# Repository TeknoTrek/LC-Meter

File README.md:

# DIY LC Meter Project

This project demonstrates how to build a DIY LC Meter capable of measuring inductance (L) and capacitance (C) values using an Arduino Nano, an LM311 comparator, and a 16x2 LCD display. The LC Meter is designed to be simple, affordable, and effective for electronics enthusiasts and DIY hobbyists. It is suitable for learning about measurement principles while also being a practical tool.

## Project Highlights:

### 1 - Circuit Schematic
A detailed circuit diagram explains the working principle and interconnection of components such as the LM311 comparator, relay, calibration buttons, and measurement probes. The schematic provides a foundation for assembling the hardware.

### 2 - PCB Design
A professionally designed single-layer PCB created with KiCad ensures clean routing and minimizes interference. It includes detailed silkscreen labels for easy assembly and debugging.

### 3 - 3D Model
A realistic 3D representation of the completed PCB with components mounted, offering a clear view of the final product and component placement.

### 4 - Firmware
The Arduino Nano is programmed with custom firmware to calculate inductance and capacitance values. Measurements are displayed on a 16x2 LCD in real time.

### 5 - Calibration and Functionality
The project includes functionality for calibration, zeroing, and easy measurement. Buttons on the PCB allow users to fine-tune settings for accurate results.

---

### Features:
- Precise Measurements: Measure a wide range of inductance and capacitance values.
- User-Friendly Interface: Includes a 16x2 LCD display for real-time measurement results and intuitive feedback.
- Adjustable Calibration: Easily calibrate the device for accurate readings using the on-board calibration buttons.
- Compact and Portable: The design is compact, making it easy to use in different workspaces or carry for fieldwork.

### Instructions:
### Prepare the PCB:
Download the provided Gerber files and manufacture the PCB, or use the KiCad design to etch your own board.

### Assemble Components:
Place and solder all components as per the silkscreen labels on the PCB.

### Upload Firmware:
Use the Arduino IDE to upload the provided sketch to your Arduino Nano. Ensure all libraries are correctly installed.

### Power and Calibration:
Connect the LC Meter to a 5V power source via USB or the provided input terminals. Calibrate the device using the calibration and zero buttons for precise results.

### Start Measuring:
Connect your inductors or capacitors to the respective terminals (Lx or Cx) and observe the measurement results on the LCD.

## Watch the Build Process

You can watch the full build process of this DIY LC Meter on my YouTube channel [**Teknotrek**](https://www.youtube.com/@TeknoTrek). Click the link below to see how the circuit is assembled, soldered, and tested:

[Watch on YouTube](https://youtu.be/YbbpxDlLRkQ)

## Files Included:
- Circuit schematic
- PCB design files (KiCad)
- 3D PCB model
- Arduino firmware
- Documentation with detailed assembly and usage instructions

## Circuit Schematic

## PCB Layout

## 3D Model

## GitHub Repository:
All project files, including schematics, PCB designs, 3D models, and source code, are available on GitHub.

Check out the project here: [**Teknotrek**](https://www.youtube.com/@TeknoTrek)

This project is perfect for anyone interested in electronics, DIY tools, or Arduino projects. Whether you are a beginner or an experienced maker,this LC Meter provides a hands-on learning experience and a functional tool for your electronics toolkit!

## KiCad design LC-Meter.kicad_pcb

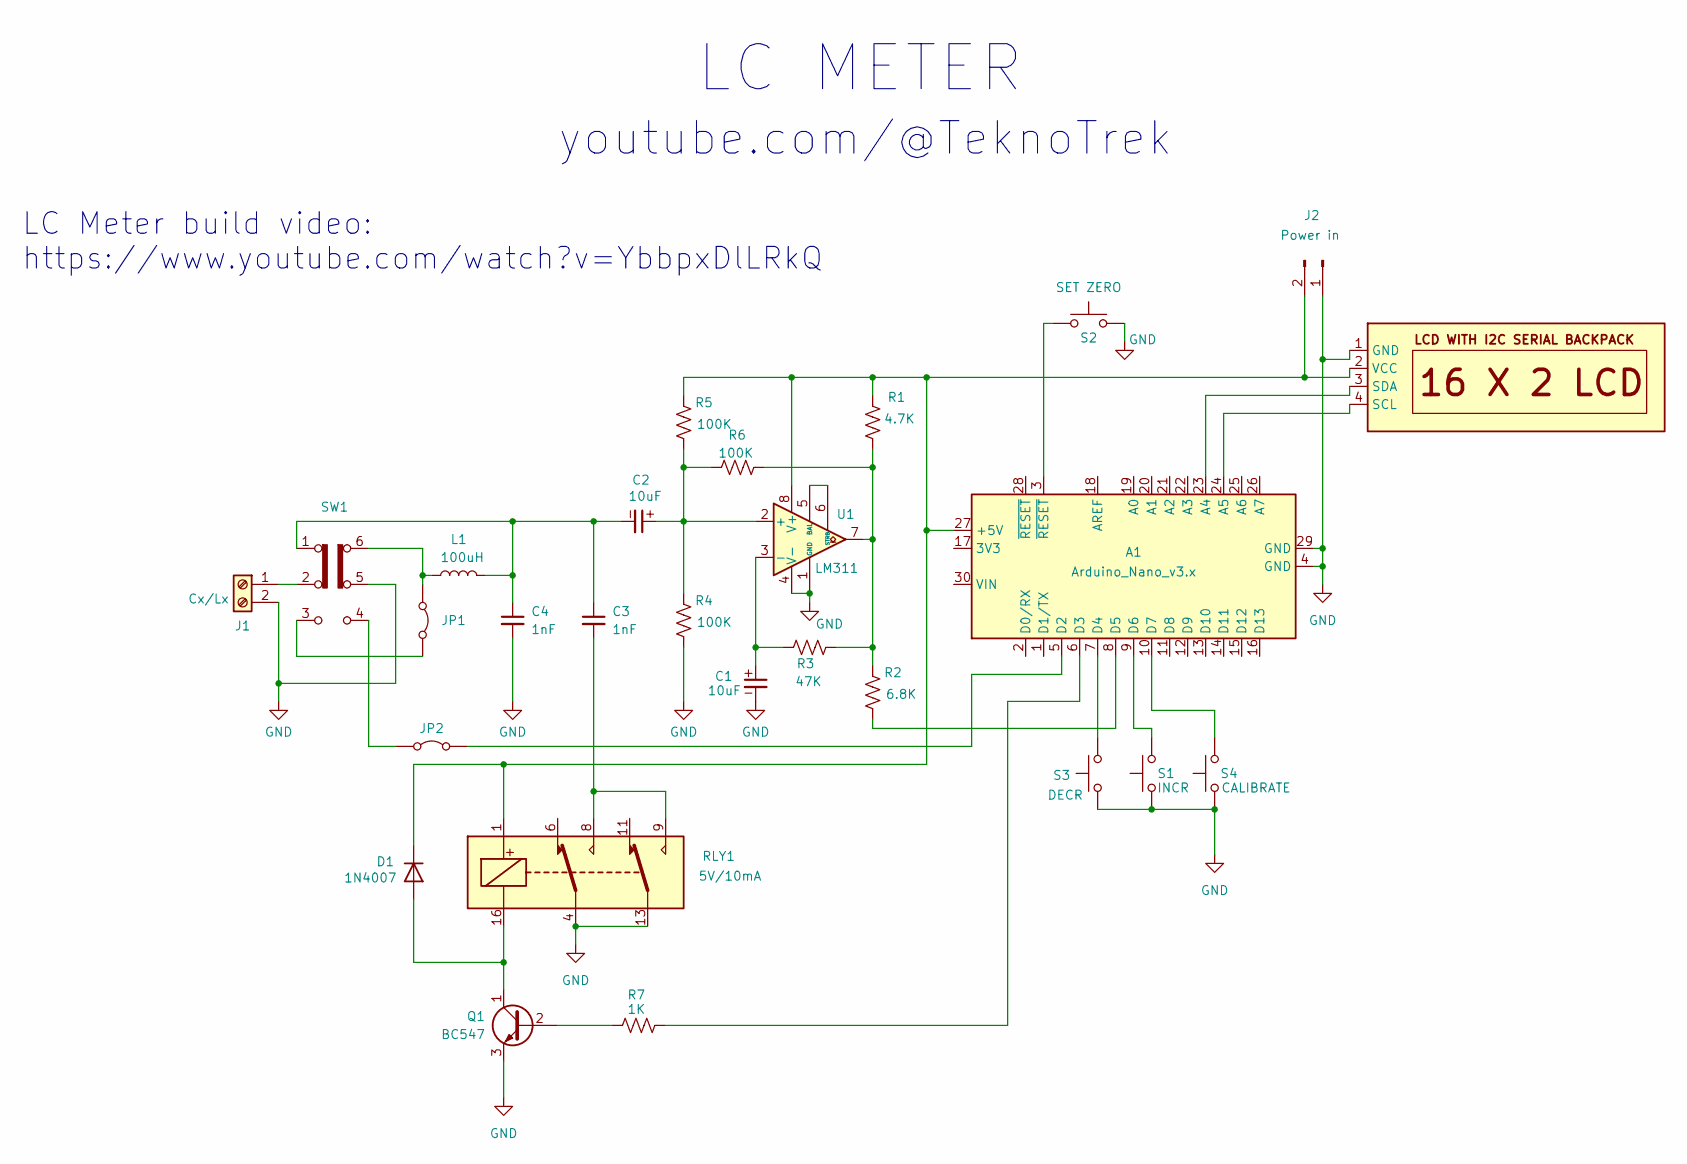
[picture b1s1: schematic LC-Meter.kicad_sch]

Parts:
A1: Arduino_Nano_v3.x; Arduino_Nano
C1, C2: 10uF; CP_Radial_Tantal_D4.5mm_P2.50mm
C3, C4: 1nF; CP_Radial_Tantal_D5.0mm_P5.00mm
D1: 1N4007; D_DO-41_SOD81_P10.16mm_Horizontal
DS1: WC1602A-I2C
J1: Cx/Lx; TerminalBlock_bornier-2_P5.08mm
J2: Power in; PinSocket_1x02_P2.54mm_Vertical
JP1, JP2: Jumper_2; R_Axial_DIN0207_L6.3mm_D2.5mm_P10.16mm_Horizontal
L1: 100uH; L_Axial_L5.3mm_D2.2mm_P10.16mm_Horizontal_Vishay_IM-1
Q1: BC547; TO-92_Wide
R1: 4.7K; R_Axial_DIN0207_L6.3mm_D2.5mm_P10.16mm_Horizontal
R2: 6.8K; R_Axial_DIN0207_L6.3mm_D2.5mm_P10.16mm_Horizontal
R3: 47K; R_Axial_DIN0207_L6.3mm_D2.5mm_P10.16mm_Horizontal
R4, R5, R6: 100K; R_Axial_DIN0207_L6.3mm_D2.5mm_P10.16mm_Horizontal
R7: 1K; R_Axial_DIN0207_L6.3mm_D2.5mm_P10.16mm_Horizontal
RLY1: 5V/10mA; TIANBO-HJR1-2CL-05V-footer
S1: INCR; SW_PUSH-12mm
S2: SET ZERO; SW_PUSH-12mm
S3: DECR; SW_PUSH-12mm
S4: CALIBRATE; SW_PUSH-12mm
SW1: SW_Slide_DPDT; SW_CK_
U1: LM311; DIP-8_W7.62mm

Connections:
GND: A1.4 (GND), A1.29 (GND), C1.2, C4.2, DS1.1 (GND), J1.2, J2.1, Q1.3 (E), R4.2, RLY1.4, RLY1.13, S1.1, S2.2, S3.1, S4.1, SW1.5 (B), U1.1 (GND), U1.4 (V-)
unnamed: A1.27 (+5V), D1.1 (K), DS1.2 (VCC), J2.2, R1.1, R5.1, RLY1.1, U1.8 (V+)
unnamed: A1.23 (A4), DS1.3 (SDA)
unnamed: A1.24 (A5), DS1.4 (SCL)
unnamed: A1.5 (D2), JP2.2 (B)
unnamed: A1.6 (D3), R7.2
unnamed: A1.7 (D4), S3.2
unnamed: A1.8 (D5), R2.2
unnamed: A1.9 (D6), S1.2
unnamed: A1.10 (D7), S4.2
unnamed: A1.3 (~RESET), S2.1
unnamed: C2.2, C3.1, C4.1, L1.2, SW1.1 (A)
unnamed: C3.2, RLY1.8, RLY1.9
unnamed: D1.2 (A), Q1.1 (C), RLY1.16
unnamed: J1.1, SW1.2 (B)
unnamed: JP1.1 (A), L1.1, SW1.6 (C)
unnamed: JP1.2 (B), SW1.3 (C)
unnamed: JP2.1 (A), SW1.4 (A)
unnamed: Q1.2 (B), R7.1
unnamed: R1.2, R2.1, R3.2, R6.2, U1.7
unnamed: C2.1, R4.1, R5.2, R6.1, U1.2 (+)
unnamed: C1.1, R3.1, U1.3 (-)
unnamed: U1.5 (BAL), U1.6 (STRB)

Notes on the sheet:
LC Meter build video: https://www.youtube.com/watch?v=YbbpxDlLRkQ
youtube.com/@TeknoTrek
LC METER

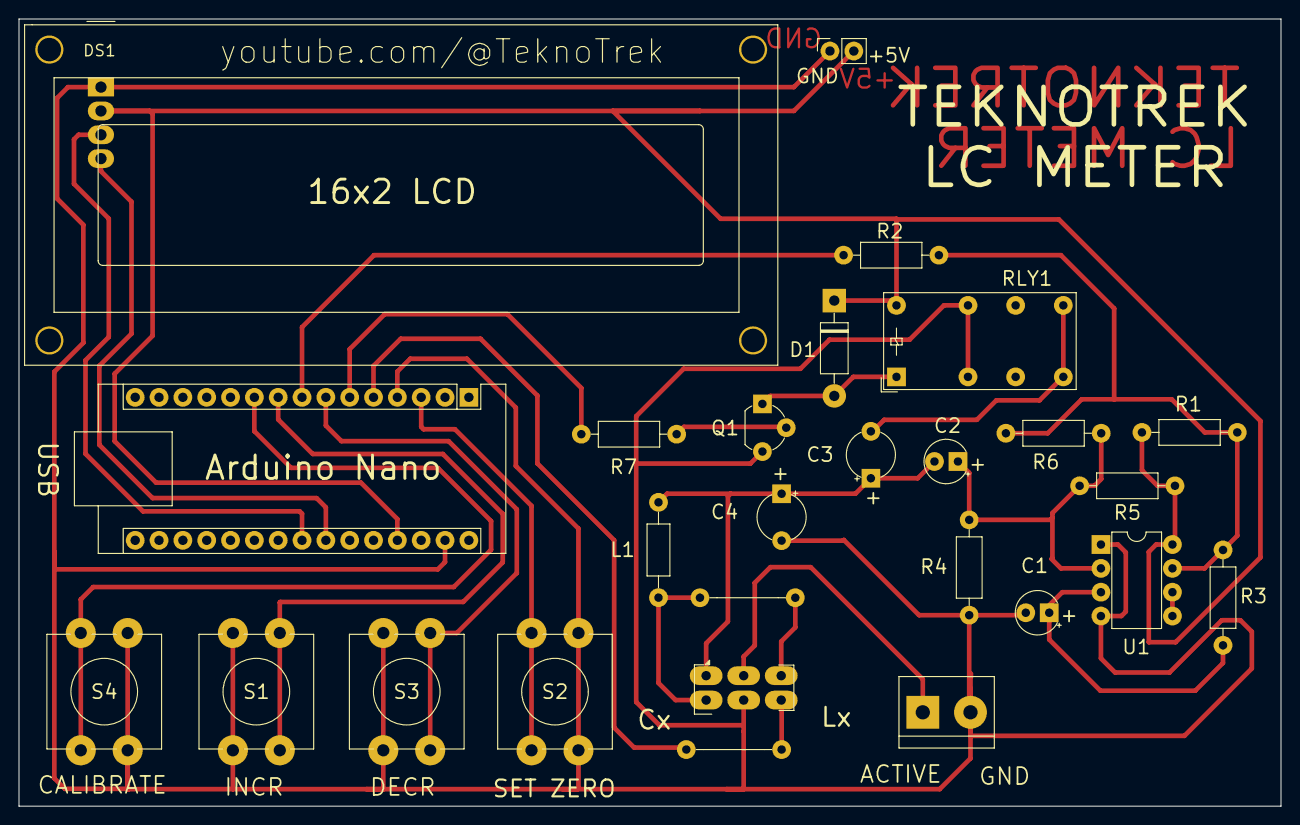
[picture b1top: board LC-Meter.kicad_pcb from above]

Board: 2 copper layers, 134.5 x 83.9 mm, 27 parts (0 on the bottom side), 23 nets.
